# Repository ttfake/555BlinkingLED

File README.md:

# 555BlinkingLED
A simple KiCad project that blinks an LED with a 555 timer.

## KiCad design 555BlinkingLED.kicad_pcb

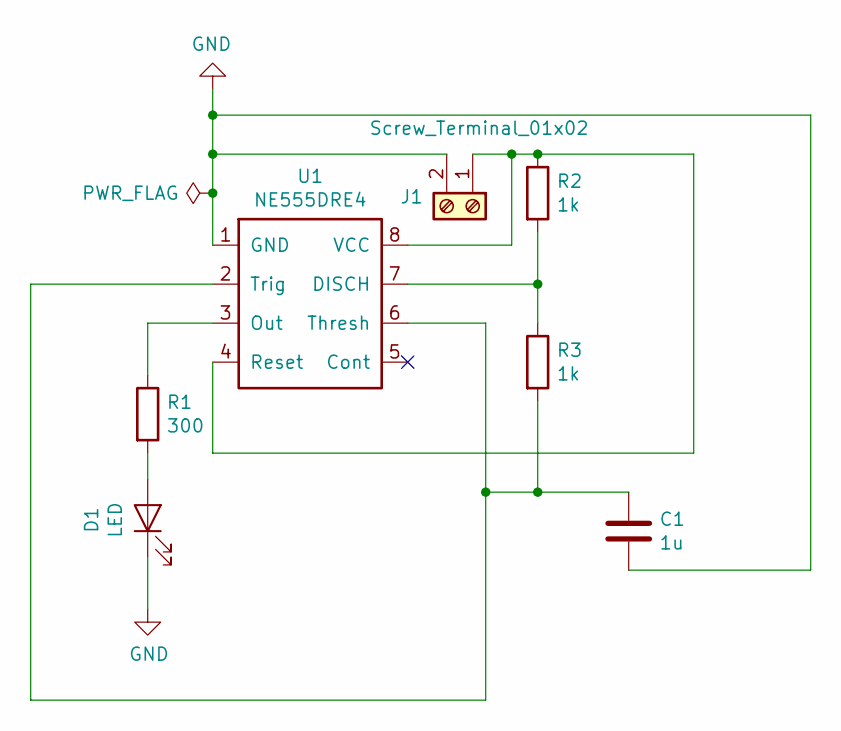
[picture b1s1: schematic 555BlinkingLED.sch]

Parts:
C1: 1u; C_0603_HandSoldering
D1: LED; LED_0603_HandSoldering
J1: Screw_Terminal_01x02; TerminalBlock_Altech_AK300-2_P5.00mm
R1: 300; R_0603_HandSoldering
R2, R3: 1k; R_0603_HandSoldering
U1: NE555DRE4; SOIC-8_3.9x4.9mm_Pitch1.27mm

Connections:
GND: C1.2, D1.1 (K), J1.2, U1.1 (GND)
unnamed: C1.1, R3.2, U1.2 (Trig), U1.6 (Thresh)
unnamed: D1.2 (A), R1.2
unnamed: J1.1, R2.1, U1.4 (Reset), U1.8 (VCC)
unnamed: R1.1, U1.3 (Out)
unnamed: R2.2, R3.1, U1.7 (DISCH)

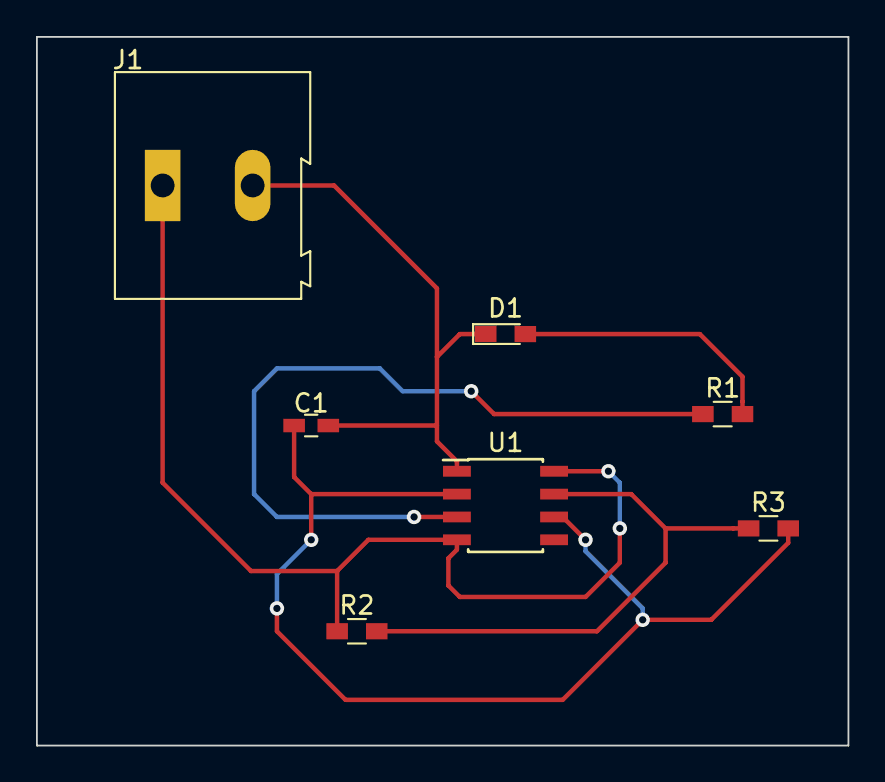
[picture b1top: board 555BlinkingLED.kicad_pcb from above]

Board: 2 copper layers, 45.1 x 39.4 mm, 7 parts (0 on the bottom side), 6 nets.

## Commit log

2019-11-11 Complete KiCad Project
